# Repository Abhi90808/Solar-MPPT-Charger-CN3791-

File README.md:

# Solar MPPT Charger (CN3791)

A solar Li-ion battery charger PCB using the CN3791 MPPT IC, designed in KiCad 8. Optimized for single-cell Li-ion charging from small solar panels with automatic maximum power point tracking.

---

## Features
- CN3791 MPPT solar charging IC
- Single-cell Li-ion / Li-Po charging (4.2V)
- MPPT for maximum solar panel efficiency
- Charging current up to 2A (adjustable)
- Charge status LED indicator
- Compact SMD design

## Specifications

| Parameter | Value |
|-----------|-------|
| Charging IC | CN3791 |
| Solar Input Voltage | 4.5V – 6.5V (typical 5V panel) |
| Battery Type | Single-cell Li-ion / Li-Po |
| Charge Voltage | 4.2V |
| Max Charge Current | 2A (set by RPROG) |
| MPPT | Yes (resistor-programmable) |
| Efficiency | Up to 90% |
| PCB Layers | 2 |
| Designed With | KiCad 8 |

## Project Structure

```
├── Schematic/       # KiCad schematic (.kicad_sch, PDF)
├── PCB/             # PCB layout (.kicad_pcb, .kicad_pro)
├── Gerbers/         # Fabrication files
├── BOM/             # Bill of materials (CSV)
├── 3D/              # 3D model (.step)
└── Images/          # PCB renders and schematic screenshots
```

## How It Works

The CN3791 tracks the solar panel's maximum power point using a resistor-set voltage reference on the MPPT pin. It implements CC/CV charging — constant current until the battery reaches 4.2V, then switches to constant voltage. This ensures the solar panel always operates near its peak power output regardless of battery state.

## MPPT Voltage Setting

The MPPT input voltage is set by a resistor divider on the MPPT pin:

```
V_MPPT = 1.205 × (1 + R1/R2)
```

For a 5V panel with ~4.5V MPP: use R1 = 270kΩ and R2 = 100kΩ.

## Bill of Materials (Summary)

| Component | Value | Qty |
|-----------|-------|-----|
| MPPT Charger IC | CN3791 | 1 |
| Inductor | 10µH | 1 |
| Schottky Diode | SS14 | 1 |
| Input Capacitor | 10µF / 10V | 1 |
| Output Capacitor | 47µF / 10V | 1 |
| RPROG Resistor | 3.9kΩ (500mA) | 1 |
| MPPT Resistors | 270kΩ, 100kΩ | 2 |
| LED | Green | 1 |

## Fabrication

Gerber files are in `/Gerbers`, ready for JLCPCB, PCBWay, or similar.

## License

This project is licensed under the [CERN Open Hardware Licence Version 2 - Strongly Reciprocal (CERN OHL-S v2)](https://ohwr.org/cern_ohl_s_v2.txt).

## Author

**Abhi90808** — [GitHub Profile](https://github.com/Abhi90808)

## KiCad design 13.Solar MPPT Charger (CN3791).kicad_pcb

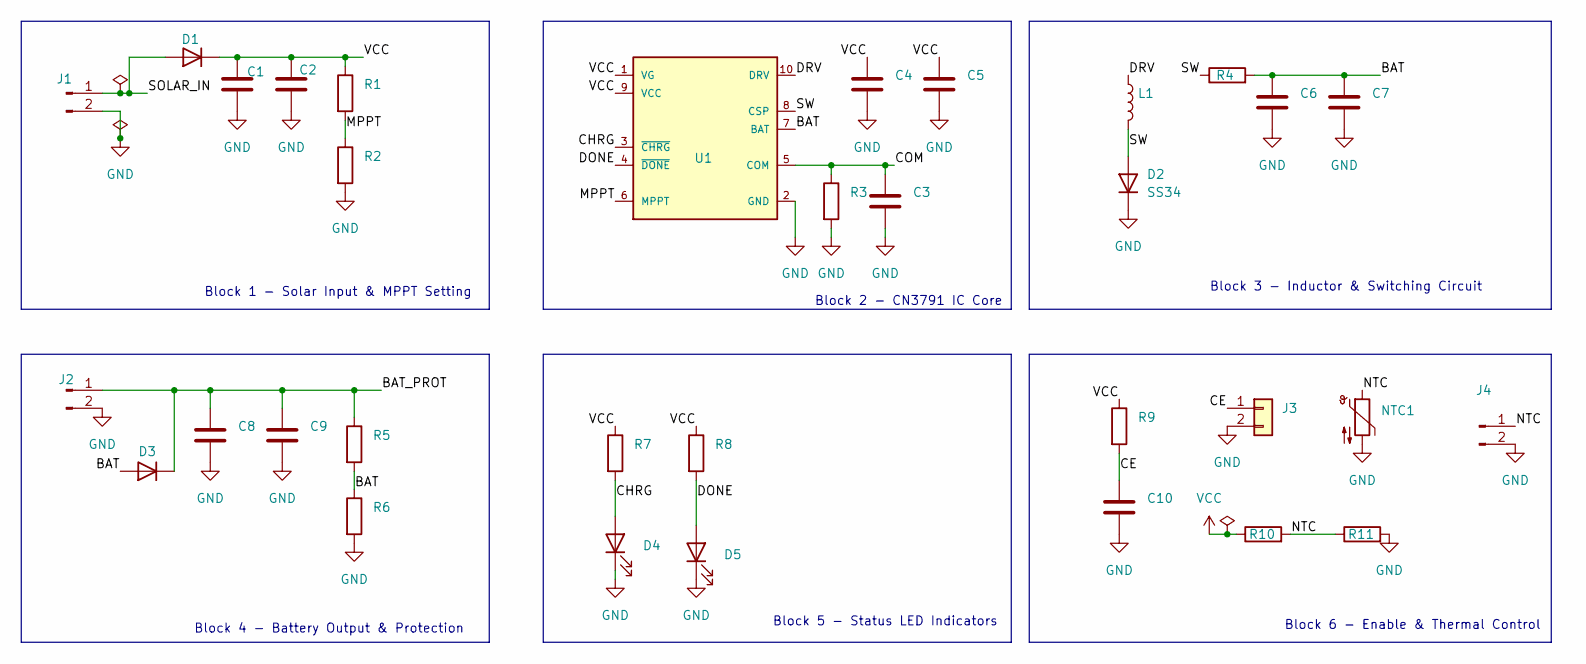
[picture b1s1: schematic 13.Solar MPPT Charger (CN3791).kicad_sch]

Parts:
C1: 100uf; C_1210_3225Metric
C2, C5: 100nf; C_0402_1005Metric
C3: 10nf; C_0402_1005Metric
C4: 10uF; C_0402_1005Metric
C6, C8: 100uF; C_1210_3225Metric
C7, C9, C10: 100nF; C_0402_1005Metric
D1, D3: 1N5819; D_SOD-123
D2: SS34; D_SMA
D4: RED; LED_0805_2012Metric
D5: GREEN; LED_0805_2012Metric
J1: SOLAR_INPUT; PinHeader_1x02_P2.54mm_Vertical
J2: BATTERY; PinHeader_1x02_P2.54mm_Vertical
J3: CE_CTRL; PinHeader_1x02_P2.54mm_Vertical
J4: NTC_CONN; PinHeader_1x02_P2.54mm_Vertical
L1: 10uH; L_Bourns_SRR1260
NTC1: 10k_NTC; R_0402_1005Metric
R1: 100k; R_0402_1005Metric
R2: 39k; R_0402_1005Metric
R3: 10K; R_0402_1005Metric
R4: 0.1R; R_2512_6332Metric
R5, R6, R9, R10, R11: 10k; R_0402_1005Metric
R7, R8: 4.7k; R_0402_1005Metric
U1: CN3791; SOIC-10_3.9x4.9mm_P1mm

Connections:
/BAT: C6.1, C7.1, D3.2 (A), R4.2, R5.2, R6.1, U1.7 (BAT)
/BAT_PROT: C8.1, C9.1, D3.1 (K), J2.1, R5.1
/CE: C10.1, J3.1, R9.2
/CHRG: D4.2 (A), R7.2, U1.3 (~CHRG)
/COM: C3.1, R3.1, U1.5 (COM)
/DONE: D5.2 (A), R8.2, U1.4 (~DONE)
/DRV: L1.1, U1.10 (DRV)
/MPPT: R1.2, R2.1, U1.6 (MPPT)
/NTC: J4.1, NTC1.1, R10.2, R11.1
/SOLAR_IN: D1.2 (A), J1.1
/SW: D2.2 (A), L1.2, R4.1, U1.8 (CSP)
GND: C1.2, C2.2, C3.2, C4.2, C5.2, C6.2, C7.2, C8.2, C9.2, C10.2, D2.1 (K), D4.1 (K), D5.1 (K), J1.2, J2.2, J3.2, J4.2, NTC1.2, R2.2, R3.2, R6.2, R11.2, U1.2 (GND)
VCC: C1.1, C2.1, C4.1, C5.1, D1.1 (K), R1.1, R7.1, R8.1, R9.1, R10.1, U1.1 (VG), U1.9 (VCC)

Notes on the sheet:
Block 6 - Enable & Thermal Control
Block 3 - Inductor & Switching Circuit
Block 4 - Battery Output & Protection
Block 1 - Solar Input & MPPT Setting
Block 5 - Status LED Indicators
Block 2 - CN3791 IC Core

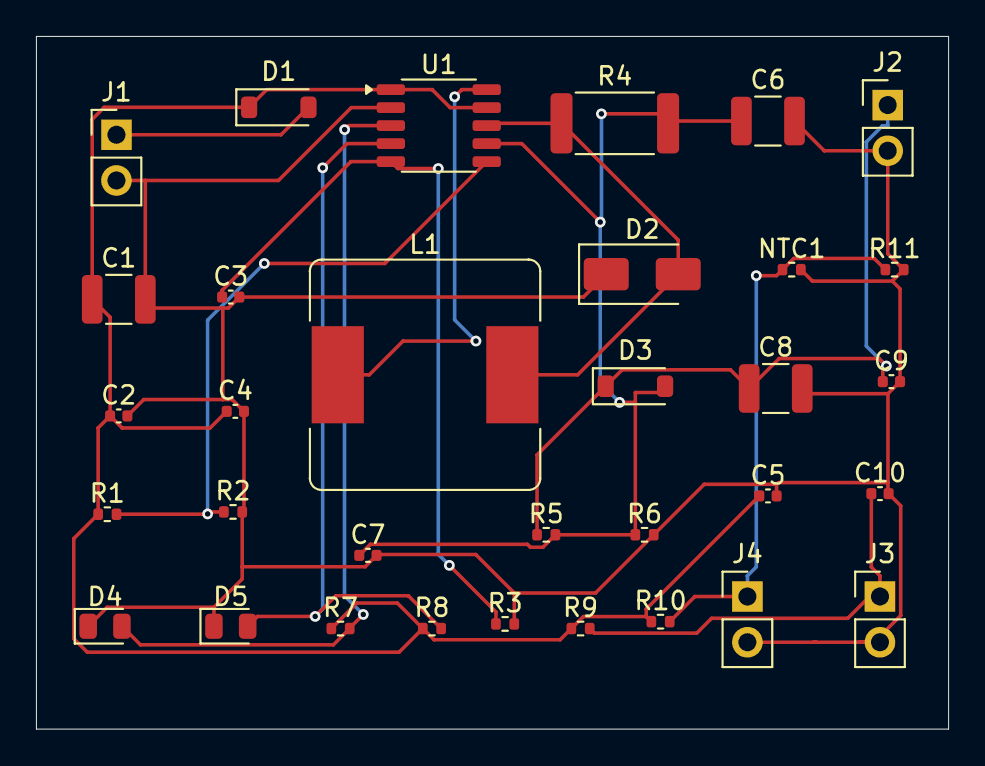
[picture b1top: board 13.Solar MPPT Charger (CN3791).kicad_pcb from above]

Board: 2 copper layers, 50.7 x 38.5 mm, 33 parts (0 on the bottom side), 13 nets.
